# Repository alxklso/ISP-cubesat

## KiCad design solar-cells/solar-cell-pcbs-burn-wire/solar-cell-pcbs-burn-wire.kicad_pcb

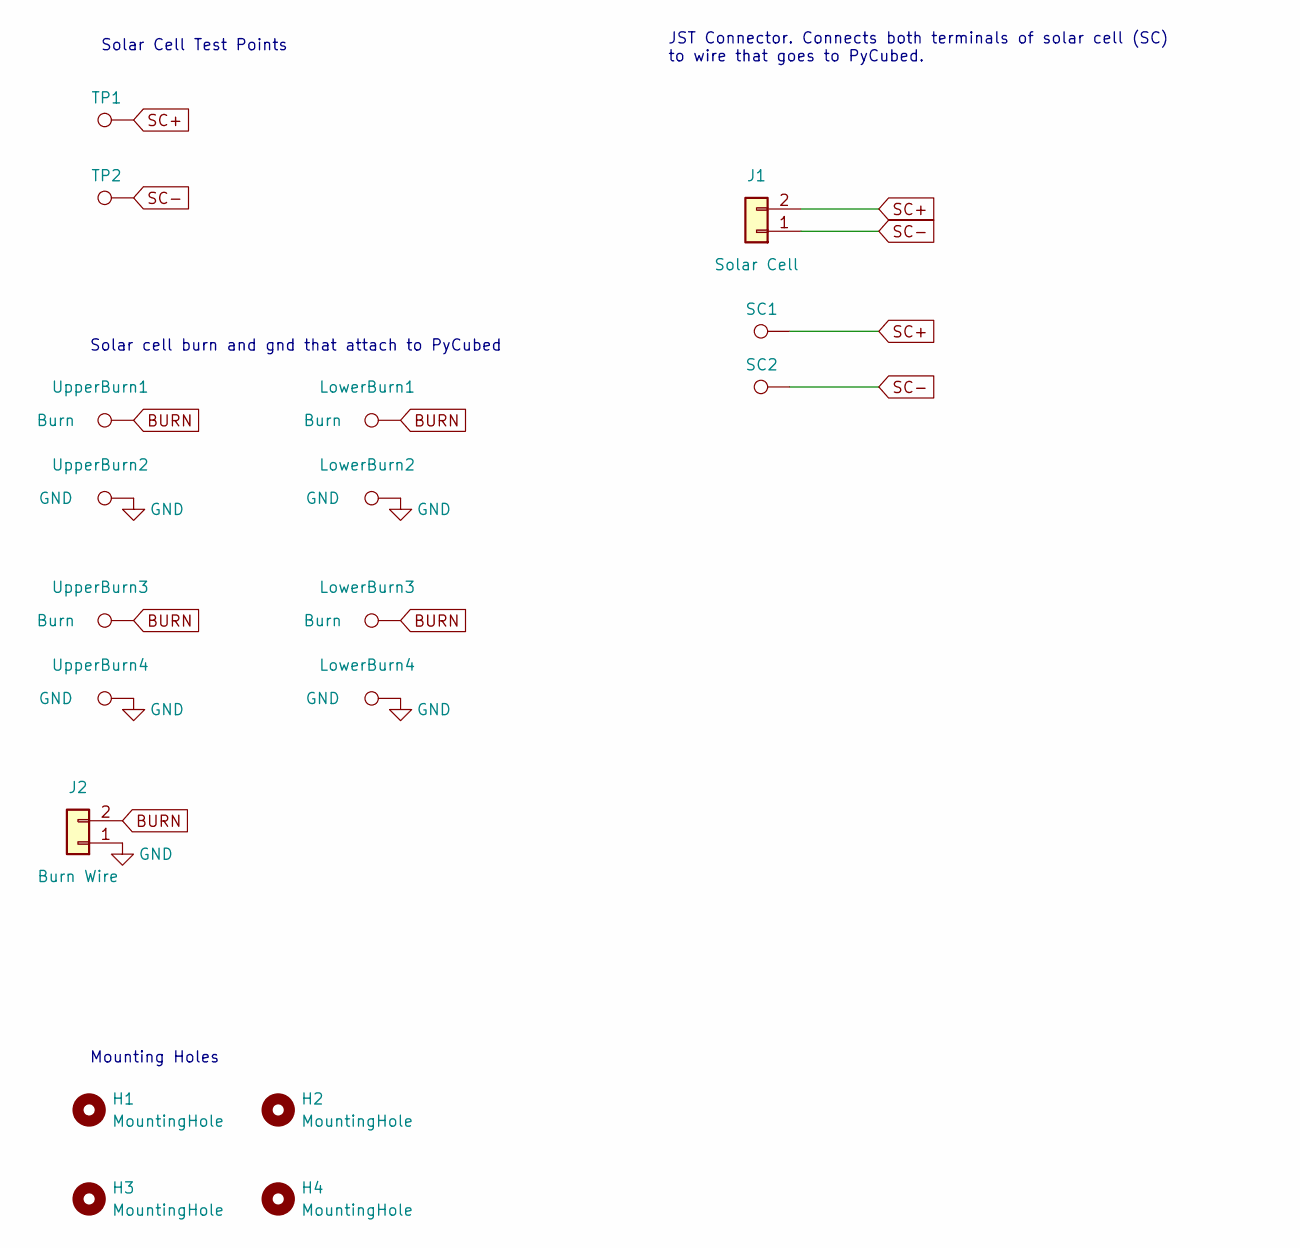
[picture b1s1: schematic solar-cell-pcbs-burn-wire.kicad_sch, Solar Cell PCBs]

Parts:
H1, H2, H3, H4: MountingHole; MountingHole_3.2mm_M3_DIN965_Pad
J1: Solar Cell; 2053380002
J2: Burn Wire; 2053380002
LowerBurn1, LowerBurn3: Burn; TestPoint_THTPad_2.0x2.0mm_Drill1.0mm
LowerBurn2, LowerBurn4: GND; TestPoint_THTPad_2.0x2.0mm_Drill1.0mm
SC1: SC+; TestPoint_THTPad_D3.0mm_Drill1.5mm
SC2: SC-; TestPoint_THTPad_D3.0mm_Drill1.5mm
TP1: SC+; TestPoint_Loop_D1.80mm_Drill1.0mm_Beaded
TP2: SC-; TestPoint_Loop_D1.80mm_Drill1.0mm_Beaded
UpperBurn1, UpperBurn3: Burn; TestPoint_THTPad_2.0x2.0mm_Drill1.0mm
UpperBurn2, UpperBurn4: GND; TestPoint_THTPad_2.0x2.0mm_Drill1.0mm

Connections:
BURN: J2.2, LowerBurn1.1, LowerBurn3.1, UpperBurn1.1, UpperBurn3.1
GND: J2.1, LowerBurn2.1, LowerBurn4.1, UpperBurn2.1, UpperBurn4.1
SC+: J1.2, SC1.1, TP1.1
SC-: J1.1, SC2.1, TP2.1

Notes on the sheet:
Solar cell burn and gnd that attach to PyCubed
Solar Cell Test Points
Mounting Holes
JST Connector. Connects both terminals of solar cell (SC) to wire that goes to PyCubed.

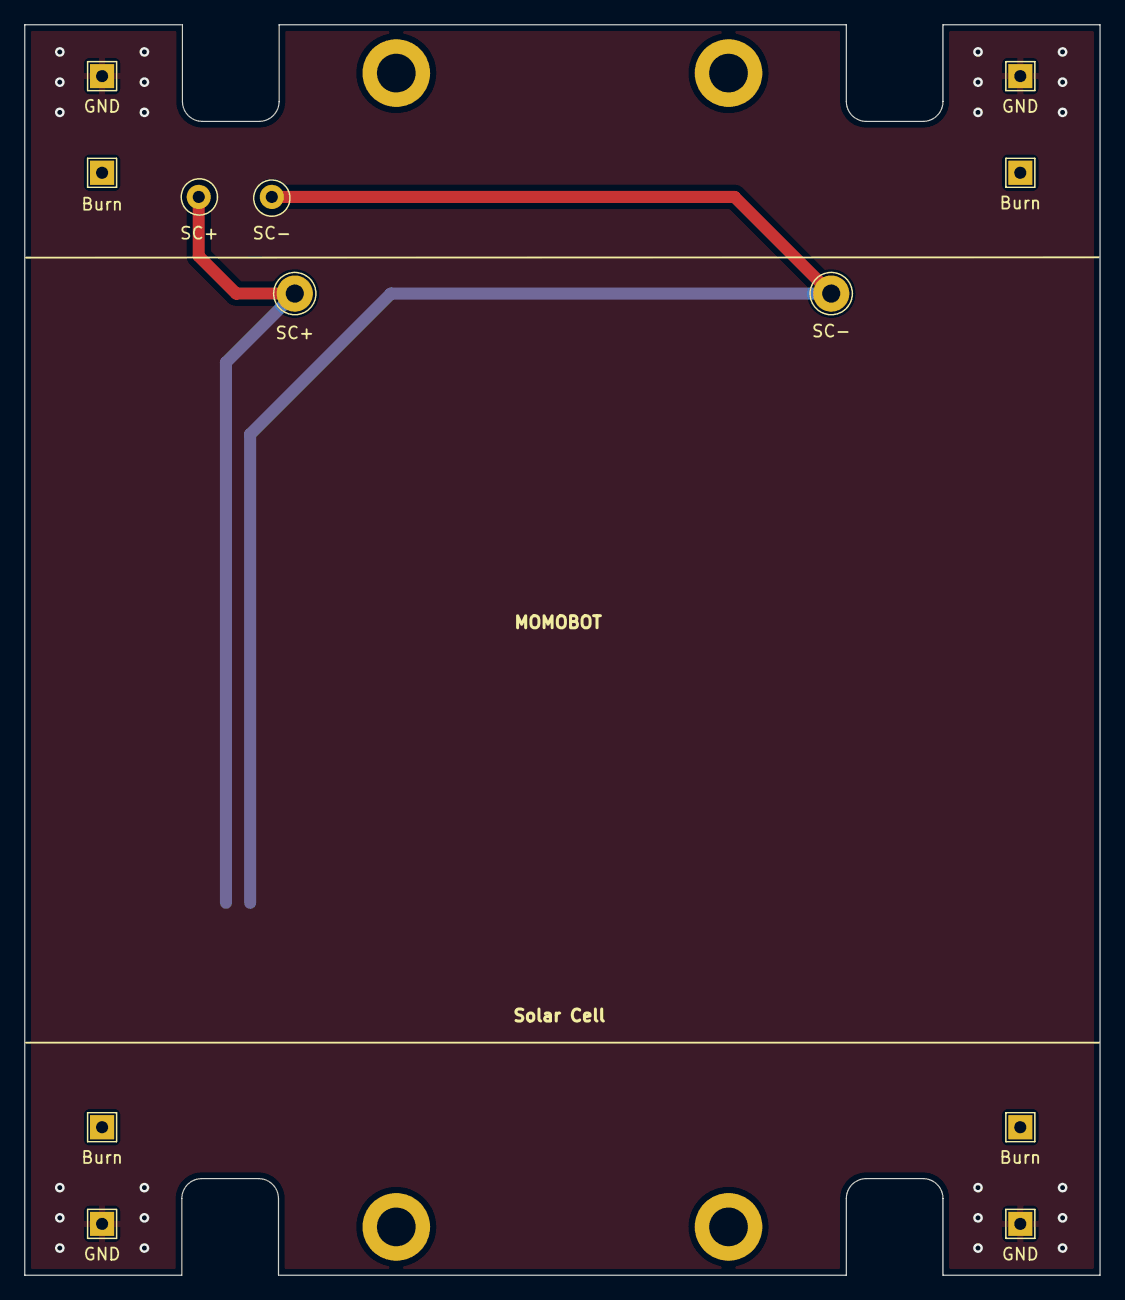
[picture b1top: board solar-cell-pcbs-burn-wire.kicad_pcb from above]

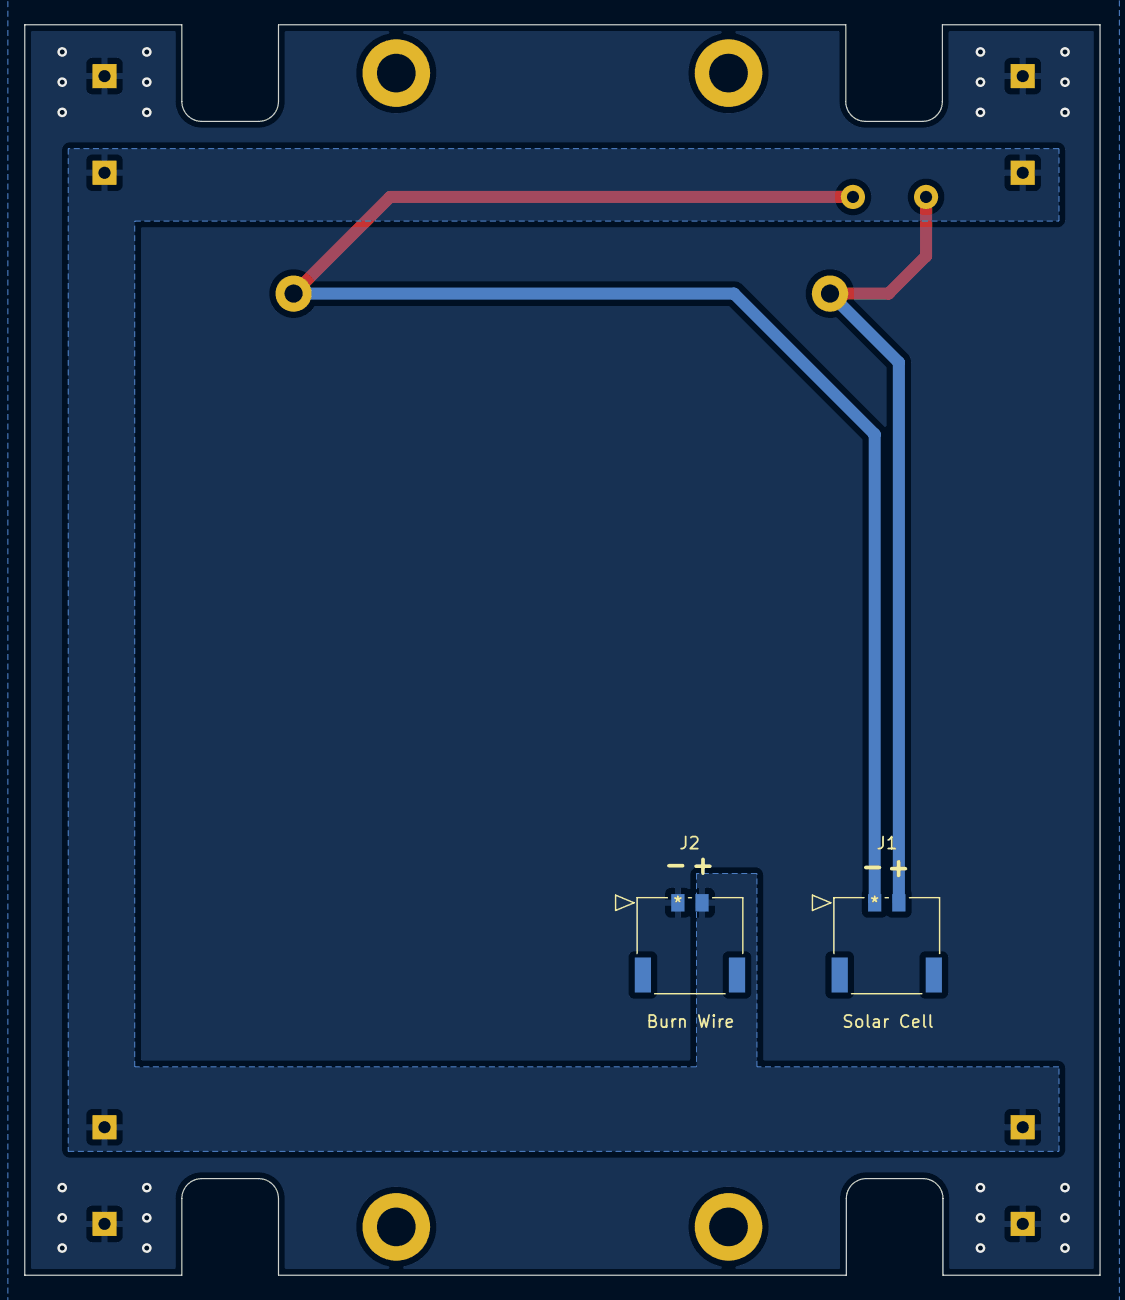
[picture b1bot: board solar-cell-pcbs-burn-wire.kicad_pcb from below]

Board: 2 copper layers, 89.0 x 103.5 mm, 18 parts (2 on the bottom side), 4 nets.

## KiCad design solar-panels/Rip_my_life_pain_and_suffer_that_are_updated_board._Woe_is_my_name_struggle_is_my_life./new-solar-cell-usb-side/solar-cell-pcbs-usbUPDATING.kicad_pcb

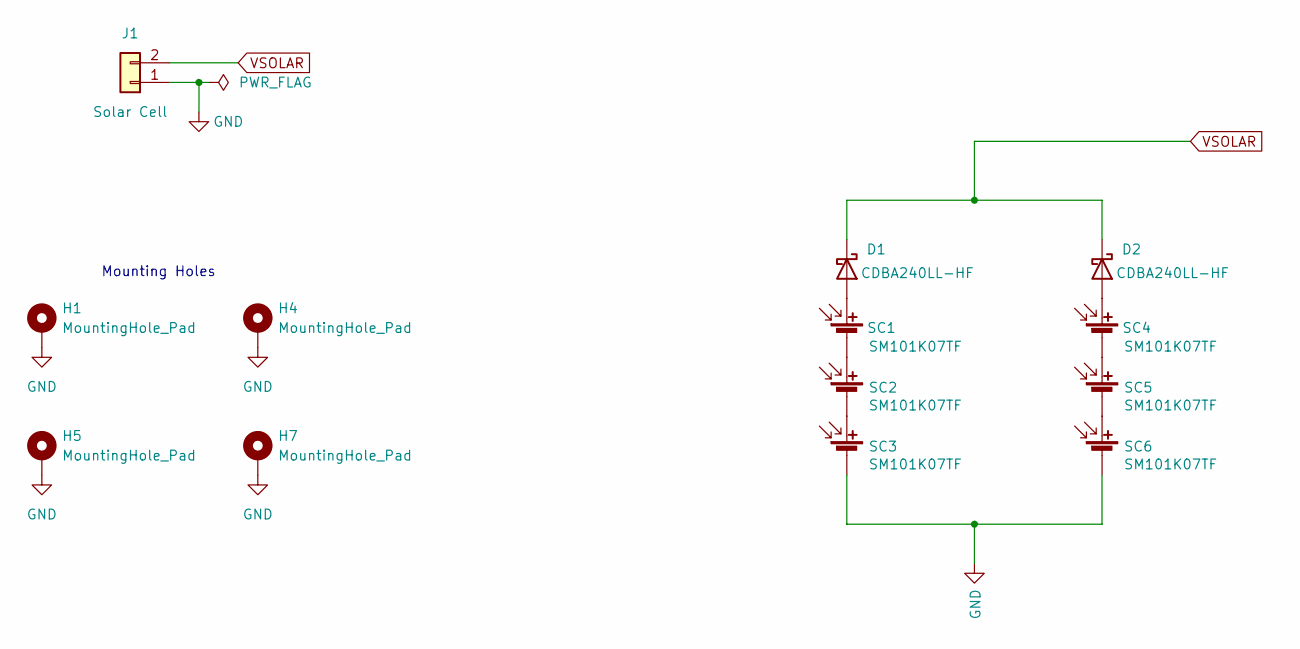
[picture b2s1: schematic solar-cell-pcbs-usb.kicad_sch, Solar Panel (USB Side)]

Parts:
D1, D2: CDBA240LL-HF; DO-214AC
H1, H4, H5, H7: MountingHole_Pad; MountingHole_3.2mm_M3_DIN965_Pad
J1: Solar Cell; 2053380002
SC1, SC2, SC3, SC4, SC5, SC6: SM101K07TF

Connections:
GND: H1.1, H4.1, H5.1, H7.1, J1.1, SC3.2 (-), SC6.2 (-); also elsewhere on the board
unnamed 1: D1.2 (A), SC1.1 (+); also elsewhere on the board
unnamed 2: D2.2 (A), SC4.1 (+); also elsewhere on the board
unnamed: SC1.2 (-), SC2.1 (+)
unnamed: SC2.2 (-), SC3.1 (+)
unnamed: SC4.2 (-), SC5.1 (+)
unnamed: SC5.2 (-), SC6.1 (+)
VSOLAR: D1.1 (K), D2.1 (K), J1.2

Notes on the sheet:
Mounting Holes

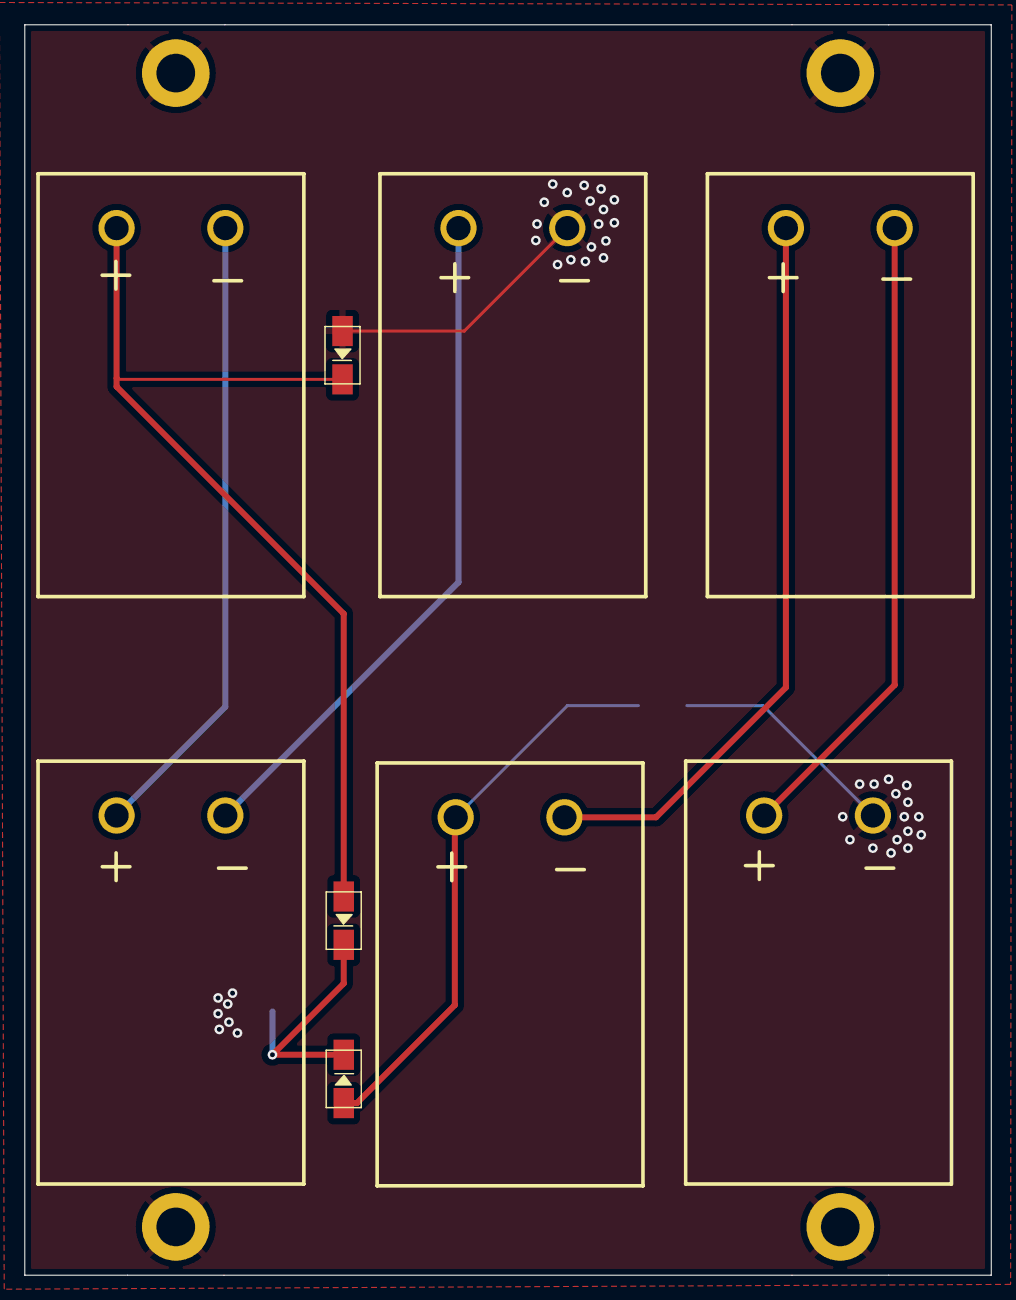
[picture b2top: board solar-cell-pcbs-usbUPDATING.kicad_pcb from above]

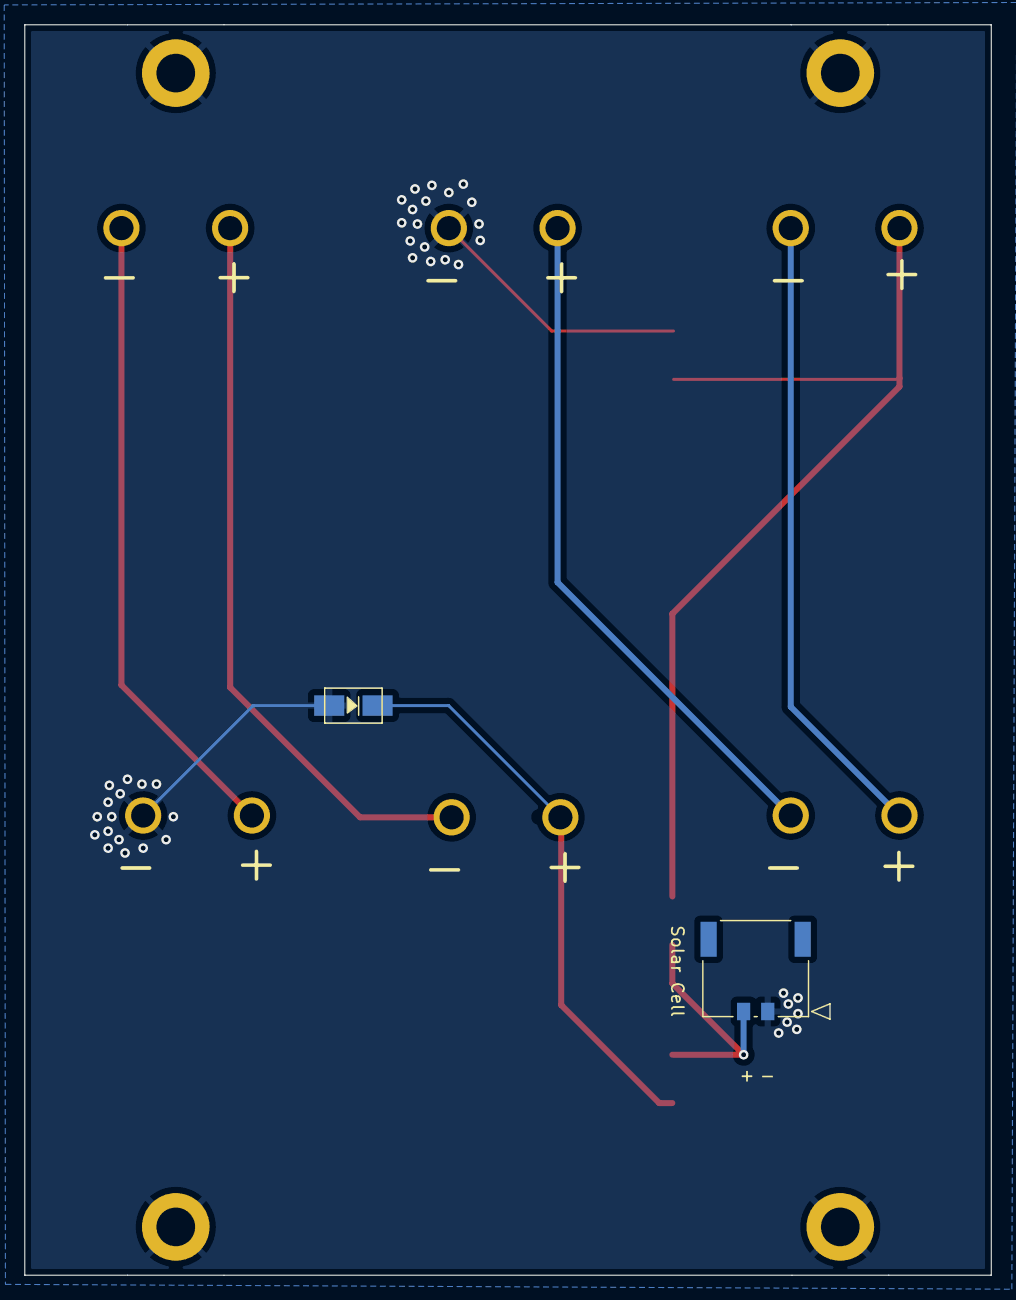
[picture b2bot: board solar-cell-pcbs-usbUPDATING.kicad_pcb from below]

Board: 2 copper layers, 80.0 x 103.5 mm, 15 parts (2 on the bottom side), 8 nets.

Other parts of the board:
D3, D4: CDBA240LL-HF; DO-214AC

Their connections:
GND: D3.2 (A), D4.2 (A); also elsewhere on the board
unnamed 1: D3.1 (K); also elsewhere on the board
unnamed 2: D4.1 (K); also elsewhere on the board

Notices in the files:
parts and their libraries:
Copyright 2021 Accelerated Designs. All rights reserved.
